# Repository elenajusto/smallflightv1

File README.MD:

# Small Flight V1

# Schematic

## Main

## Power

## Microcontroller

## Inertial Measurement Unit

## Barometer

# Design

## Ideation

## Part Selection

## Power Sizing

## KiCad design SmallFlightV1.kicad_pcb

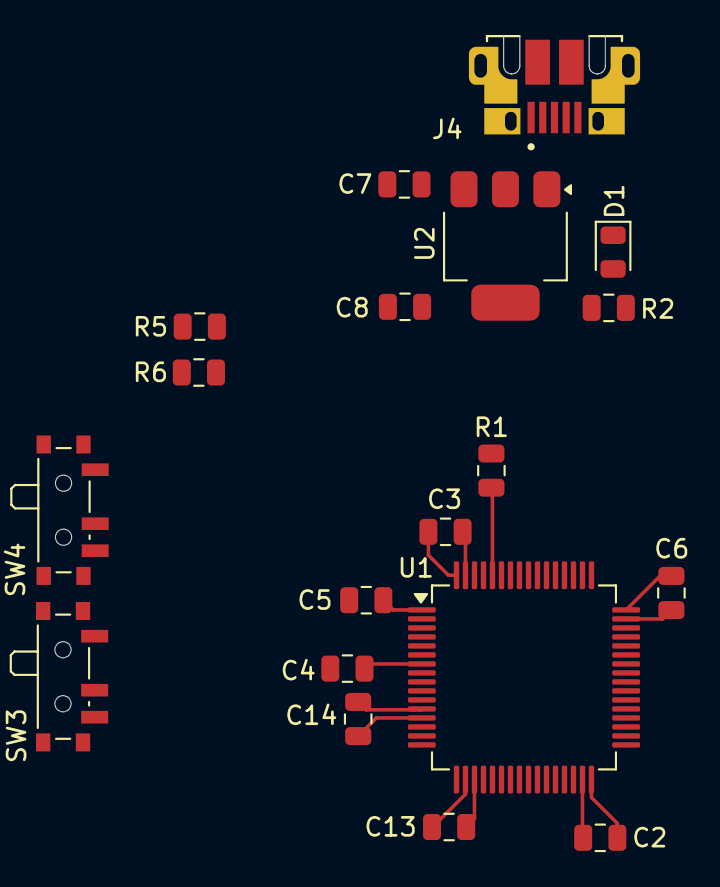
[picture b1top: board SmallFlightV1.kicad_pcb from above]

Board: 2 copper layers, 19 parts (0 on the bottom side), 12 nets.

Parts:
C2, C7, C8: 22uF; C_0805_2012Metric
C3, C4, C5, C6, C13, C14: 100nF; C_0805_2012Metric
D1: BLUE; LED_0805_2012Metric
J4: 10103592-0001LF; AMPHENOL_10103592-0001LF
R1: 10k; C_0805_2012Metric
R2, R5, R6: 1k5; C_0805_2012Metric
SW3: System Reset; SW_SPDT_PCM12
SW4: Boot Switch; SW_SPDT_PCM12
U1: STM32F446RETx; LQFP-64_10x10mm_P0.5mm
U2: AMS1117-3.3; SOT-223-3_TabPin2

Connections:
/Microcontroller/+3V3: C2.1, C3.1, C5.1, C6.1, C8.1, C13.1, C14.1, R2.1, R5.2, R6.2, SW3.1 (A), SW4.3 (C), U1.1 (VBAT), U1.13 (VDDA), U1.19 (VDD), U1.32 (VDD), U1.48 (VDD), U1.64 (VDD), U2.2 (VO)
/Microcontroller/BUZZ: U1.14 (PA0), U1.20 (PA4)
/Microcontroller/I2C1_SCL: R6.1, U1.61 (PB8)
/Microcontroller/I2C1_SDA: R5.1, U1.62 (PB9)
/Microcontroller/SW_BOOT0: R1.1, SW4.2 (B)
/Microcontroller/USB_DN: J4.3 (D+), U1.44 (PA11)
/Microcontroller/USB_DP: J4.2 (D-), U1.45 (PA12)
/Power/VBUS_MCU: C7.1, J4.1 (VDD), U2.3 (VI)
GND: C2.2, C3.2, C4.2, C5.2, C6.2, C7.2, C8.2, C13.2, C14.2, D1.1 (K), J4.5 (GND), SW3.3 (C), SW4.1 (A), U1.12 (VSSA), U1.18 (VSS), U1.31 (VSS), U1.47 (VSS), U1.63 (VSS), U2.1 (GND)
NRST: C4.1, SW3.2 (B), U1.7 (NRST)
unnamed: D1.2 (A), R2.2
unnamed: R1.2, U1.60 (BOOT0)

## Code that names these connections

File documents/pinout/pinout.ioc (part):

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Mcu.Name=STM32F446R(C-E)Tx
Mcu.Package=LQFP64
Mcu.UserName=STM32F446RETx
PA0-WKUP.GPIOParameters=GPIO_Label
PA0-WKUP.GPIO_Label=SERVO_FEEDBACK
PA0-WKUP.Signal=ADCx_IN0
PA1.GPIOParameters=GPIO_Label
PA1.GPIO_Label=SERVO_PWM
PA1.Signal=GPIO_Output
PA11.Mode=Device_Only
PA11.Signal=USB_OTG_FS_DM
PA12.Mode=Device_Only
PA12.Signal=USB_OTG_FS_DP
PA13.Mode=Serial_Wire
PA13.Signal=SYS_JTMS-SWDIO
PA14.Mode=Serial_Wire
PA14.Signal=SYS_JTCK-SWCLK
PA5.Mode=Full_Duplex_Master
PA5.Signal=SPI1_SCK
PA6.Mode=Full_Duplex_Master
PA6.Signal=SPI1_MISO
PA7.Mode=Full_Duplex_Master
PA7.Signal=SPI1_MOSI
PB6.Mode=Asynchronous
PB6.Signal=USART1_TX
PB7.Mode=Asynchronous
PB7.Signal=USART1_RX
PB8.Mode=I2C
PB8.Signal=I2C1_SCL
PB9.Mode=I2C
PB9.Signal=I2C1_SDA
PC0.GPIOParameters=GPIO_Label
PC0.GPIO_Label=BUZZ
PC0.Signal=GPIO_Output
PC1.GPIOParameters=GPIO_Label
PC1.GPIO_Label=SD_MEM_CS
PC1.Signal=GPIO_Analog
PC2.GPIOParameters=GPIO_Label
PC2.GPIO_Label=FLASH_MEM_CS
PC2.Signal=GPIO_Output
PC3.GPIOParameters=GPIO_Label
PC3.GPIO_Label=SD_DET
PC3.Signal=GPIO_Input
board=custom

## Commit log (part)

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2025-11-12 init
2025-11-16 adds tuff
2025-11-17 design documents and datasheets. estimated flight profile and selected relevant components
2025-11-17 remove unrelated files
2025-11-28 design and power information
2025-11-28 move design documents into folder
2025-11-29 diagram for power requirement
2025-11-29 battery sizing
2025-11-29 update power requirment diagram
2025-11-29 add battery to spreadsheet
2026-01-10 boilerplate stm32f4 schematic
2026-01-10 more boilerplate for stm. and also power supply using LDO and USB
2026-01-11 base mcu decoupling cap routing
